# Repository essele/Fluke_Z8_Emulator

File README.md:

# Fluke_Z8_Emulator

This is a attempt at a Z8 emulator using a PSoC processor that can be used in a Fluke 8840A multimeter, and possibly a Fluke 8842A multimeter (although I have not tested the latter.)

I'm releasing this in the hope that someone will be able to help fix the remaining issue, the code is currently in a messy state as I've not had a chance to clean it up prior to releasing it.

The pcb and schematic (KiCad format) are available in the pcb directory.

The PSoC Creator workspace is in the PSoC_Workspace directory.

** THIS IS FAR FROM PRODUCTION WORTHY **

Some known issues:

1. There is a mistake on the PCB where all the P5 pins are offset by one, this doesn't cause a problem as it can be fixed by configuration, I'll fix this on the next version.

2. The GPIB board doesn't work properly. It works ok with external trigger set, but you get intermittent strange behaviour if not using the external trigger (more info below.)

3. I'm not entirely sure everything else is ok as I've hacked around with just about everything trying to fix the GPIB problem.

I'm fairly sure the outstanding issue is one of three things:

- A mis-implemented instruction
- Still something wrong with interrupts and masking
- A timing thing

Basic Description:

** I will spend some time documenting this properly, but for now here is a very brief overview **

Port 0 and 1 -- there is a verilog module that recreates the Z8 bus protocol which controls most of port 0 and 1.

Port 2 -- port 2 is a completely normal port, handled by firmware.

Port 3 -- port 3 is made up of incoming interrupts, one input sense line, and serial and timer.

Timer 1 -- the timer is implemented using a PSoC timer, but with a verilog module attached to the output to toggle the output at the end of each timing cycle. There is also the ability to set the output to 1 to copy the behaviour of the Z8 timer.

Serial -- currently there are three different serial implementations (all attempting to fix the GPIB problem), however the behaviour is the same with all of them, so I don't think it's related. The standard PSoC UART module is used for tx, I then have two verilog RX modules. SerialDRX is implemented using a datapath component so is lightweight and needs to be used if the timer block is also used. (I'm quite pleased with this as it's super efficient as it uses the datapath for both timer and shift register!)

TODO's for the next version...

1. Redo the whole bus access bit ... there are probably quite a lot of efficiencies to be had to give us more headroom for other things.

2. New board ... different output for the clock signal. Re-look at the P3 pins ... why did they stick the debug pins in the middle of a useful port???

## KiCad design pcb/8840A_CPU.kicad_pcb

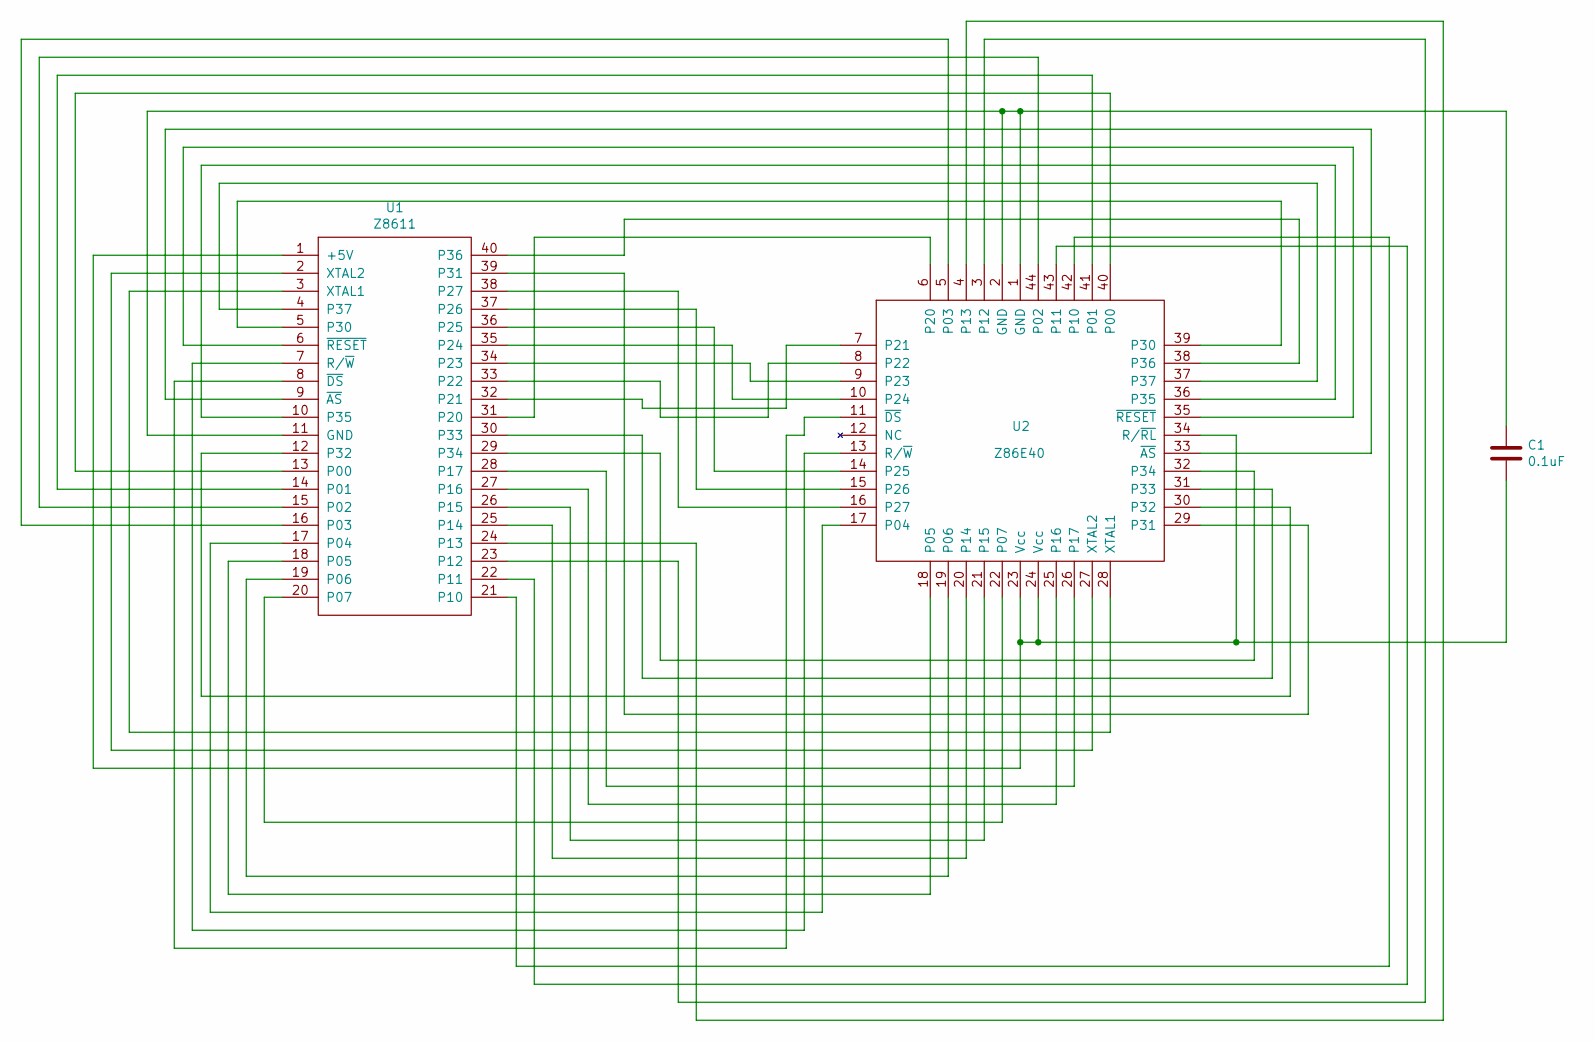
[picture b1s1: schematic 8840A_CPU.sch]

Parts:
C1: 0.1uF; C_0805_HandSoldering
U1: Z8611; DIP-40_W15.24mm
U2: Z86E40; PLCC44

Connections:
unnamed: C1.1, U1.11 (GND), U2.1 (GND), U2.2 (GND)
unnamed: C1.2, U1.1 (+5V), U2.23 (Vcc), U2.24 (Vcc), U2.34 (R/~RL)
unnamed: U1.2 (XTAL2), U2.27 (XTAL2)
unnamed: U1.3 (XTAL1), U2.28 (XTAL1)
unnamed: U1.4 (P37), U2.37
unnamed: U1.5 (P30), U2.39 (P30)
unnamed: U1.6 (~RESET), U2.35 (~RESET)
unnamed: U1.7 (R/~W), U2.13 (R/~W)
unnamed: U1.8 (~DS), U2.11 (~DS)
unnamed: U1.9 (~AS), U2.33 (~AS)
unnamed: U1.10 (P35), U2.36 (P35)
unnamed: U1.12 (P32), U2.30 (P32)
unnamed: U1.13 (P00), U2.40 (P00)
unnamed: U1.14 (P01), U2.41 (P01)
unnamed: U1.15 (P02), U2.44 (P02)
unnamed: U1.16 (P03), U2.5 (P03)
unnamed: U1.17 (P04), U2.17 (P04)
unnamed: U1.18 (P05), U2.18 (P05)
unnamed: U1.19 (P06), U2.19 (P06)
unnamed: U1.20 (P07), U2.22 (P07)
unnamed: U1.21 (P10), U2.42 (P10)
unnamed: U1.22 (P11), U2.43 (P11)
unnamed: U1.23 (P12), U2.3 (P12)
unnamed: U1.24 (P13), U2.4 (P13)
unnamed: U1.25 (P14), U2.20 (P14)
unnamed: U1.26 (P15), U2.21 (P15)
unnamed: U1.27 (P16), U2.25 (P16)
unnamed: U1.28 (P17), U2.26 (P17)
unnamed: U1.29 (P34), U2.32 (P34)
unnamed: U1.30 (P33), U2.31 (P33)
unnamed: U1.31 (P20), U2.6 (P20)
unnamed: U1.32 (P21), U2.7 (P21)
unnamed: U1.33 (P22), U2.8 (P22)
unnamed: U1.34 (P23), U2.9 (P23)
unnamed: U1.35 (P24), U2.10 (P24)
unnamed: U1.36 (P25), U2.14 (P25)
unnamed: U1.37 (P26), U2.15 (P26)
unnamed: U1.38 (P27), U2.16 (P27)
unnamed: U1.39 (P31), U2.29 (P31)
unnamed: U1.40 (P36), U2.38 (P36)

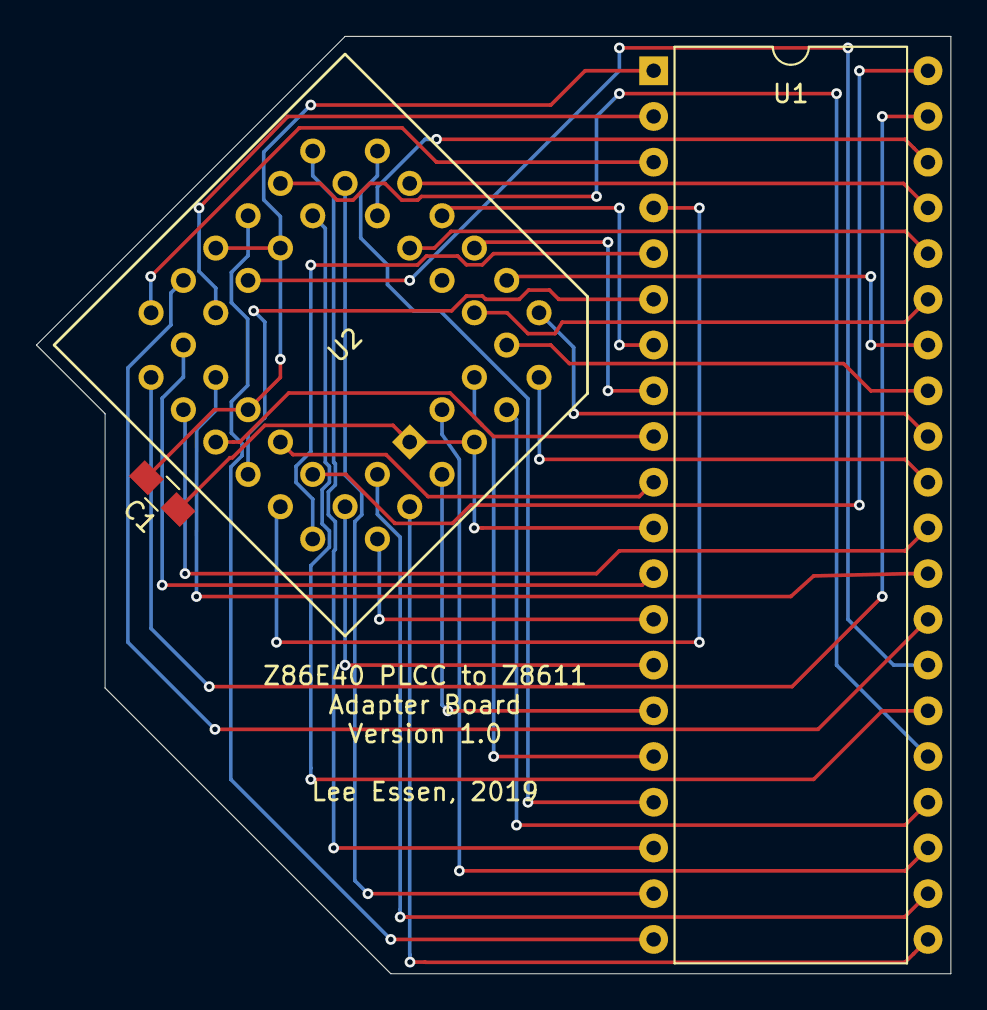
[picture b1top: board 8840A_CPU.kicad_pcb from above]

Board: 2 copper layers, 50.8 x 52.1 mm, 3 parts (0 on the bottom side), 40 nets.

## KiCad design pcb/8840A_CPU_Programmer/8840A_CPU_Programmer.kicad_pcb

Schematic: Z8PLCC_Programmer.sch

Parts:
C1: 0.1uF
C2: 0.01uF
D1: 1N5231 (5v)
D2: 1N5243 (13v)
J1: 12.5V Power In
R1, R3, R4, R5: 1K
R2: 10K
U3: Z86E40EPROM
U4: IH5042
U5: 2764; DIP-28_W15.24mm

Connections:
/5V: D1.1 (K), R1.1, U4.12
/12V5: C1.1, R3.1, U4.11, U4.16
/EPM: U3.30, U4.1, U4.3
/VCC: U3.23, U3.24, U4.15, U5.28 (VCC)
GND: C1.2, C2.2, D1.2 (A), D2.2 (A), J1.2, U3.1, U3.2, U4.4, U4.13, U4.14, U5.14 (GND)
unnamed: C2.1, U3.31, U5.1 (VPP)
unnamed: D2.1 (K), R2.1, R3.2
unnamed: J1.1, R1.2, R2.2
unnamed: R4.1, U5.22 (~OE)
unnamed: R4.2, U3.29
unnamed: R5.1, U5.20 (~CE)
unnamed: R5.2, U3.28
unnamed: U3.5, U5.7 (A3)
unnamed: U3.6, U5.11 (D0)
unnamed: U3.7, U5.12 (D1)
unnamed: U3.8, U5.13 (D2)
unnamed: U3.9, U5.15 (D3)
unnamed: U3.10, U5.16 (D4)
unnamed: U3.14, U5.17 (D5)
unnamed: U3.15, U5.18 (D6)
unnamed: U3.16, U5.19 (D7)
unnamed: U3.17, U5.6 (A4)
unnamed: U3.18, U5.5 (A5)
unnamed: U3.19, U5.4 (A6)
unnamed: U3.22, U5.3 (A7)
unnamed: U3.32, U5.25 (A8)
unnamed: U3.36, U5.24 (A9)
unnamed: U3.37, U5.23 (A11)
unnamed: U3.38, U5.21 (A10)
unnamed: U3.39, U5.27 (~PGM)
unnamed: U3.40, U5.10 (A0)
unnamed: U3.41, U5.9 (A1)
unnamed: U3.44, U5.8 (A2)

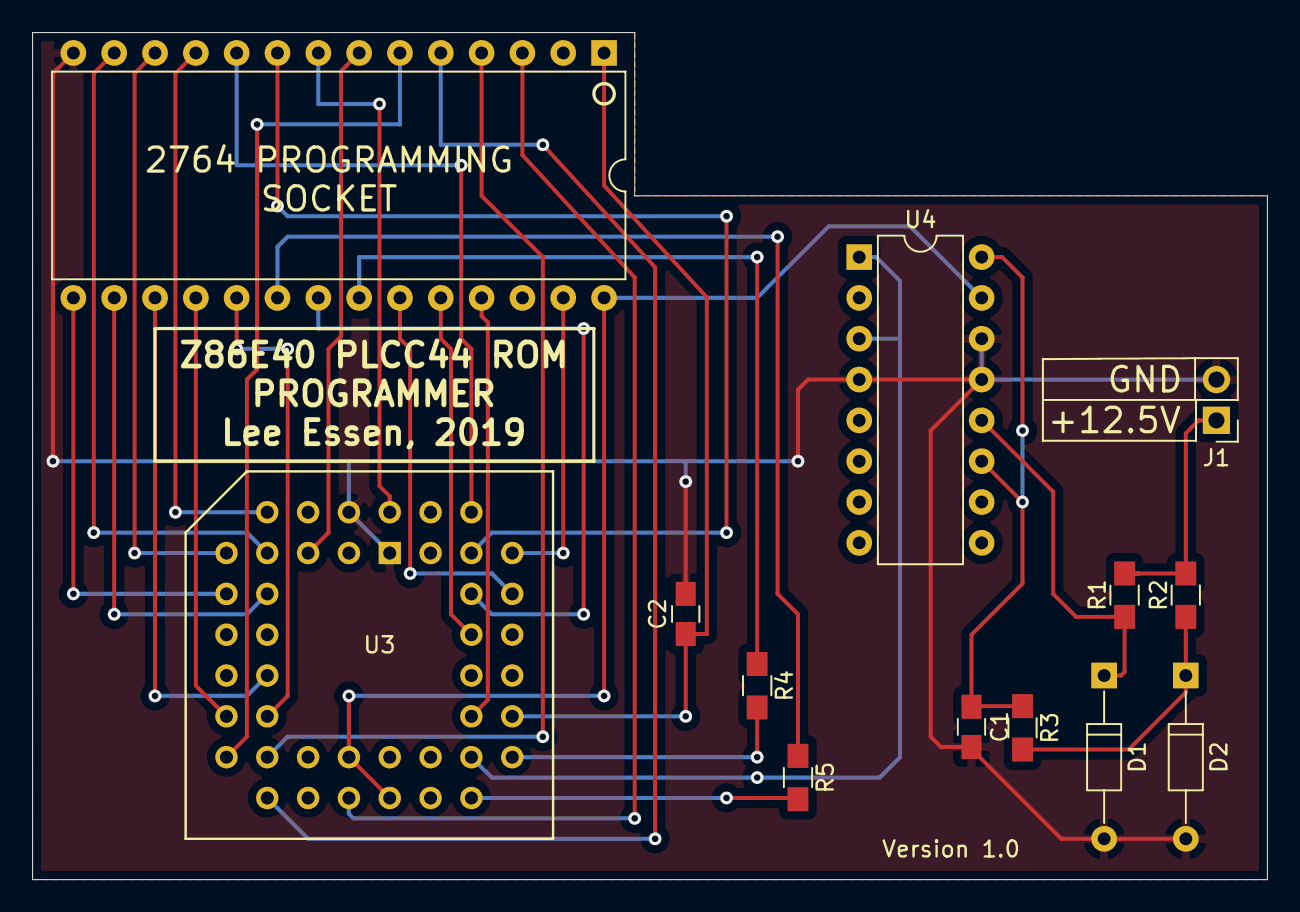
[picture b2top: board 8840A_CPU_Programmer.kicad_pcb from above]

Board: 2 copper layers, 76.8 x 52.7 mm, 13 parts (0 on the bottom side), 33 nets.

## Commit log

2019-07-07 testing push
2019-07-07 Initial workspace import
2019-07-07 another push after building to check git is in a good state
2019-07-07 more tidying
2019-07-07 why isnt this working
2019-07-07 Minor update to the bus delay code for reads
2019-07-08 Updated ExtBus to support two cycle extended bus timing (for read only)
2019-07-11 exception mechanism, plus register work
2019-07-12 cleanup of emulator code, memory read/write, exception handling
2019-07-12 IRQ code and proper firmware
2019-07-14 instruction fixes, irq fixes .. now working
2019-07-14 reworked interrupts, more responsive
2019-07-15 Set theme jekyll-theme-slate
2019-07-15 Experimenting create a new theme
2019-07-15 code tidy
2019-07-19 rework again of IRQs to try to get serial working
2019-07-22 Add master.dis for info
2019-07-22 rework again of the irq code
2019-07-24 new IRQ's again, new serial, new bus stuff
2019-07-30 added pcb and schematic
2019-07-30 further cleanup, creation of timer component
2019-07-30 new serial DP implementation
2019-07-30 simple readme
